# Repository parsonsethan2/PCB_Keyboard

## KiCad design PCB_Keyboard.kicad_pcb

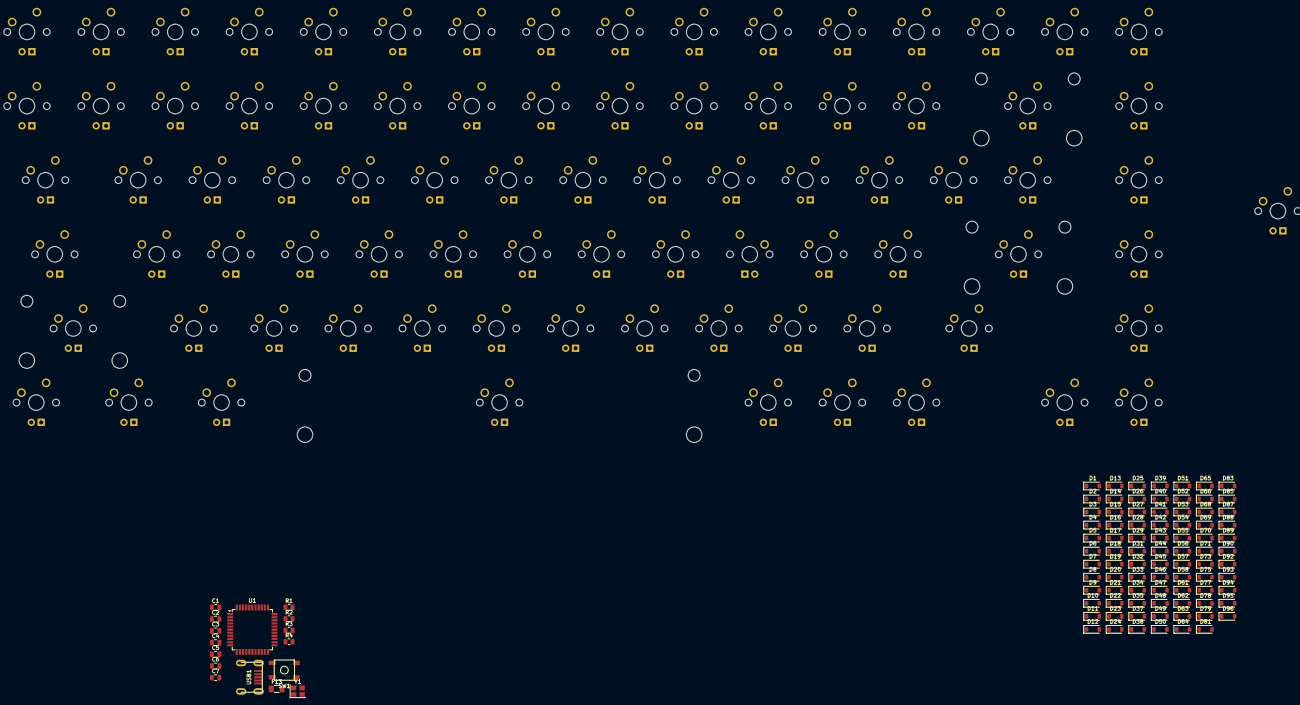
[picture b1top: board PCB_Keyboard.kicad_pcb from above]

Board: 2 copper layers, 182 parts (1 on the bottom side), 116 nets, no tracks yet.

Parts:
+/=1: MX-NoLED; MXOnly-1U
-/_1: MX-NoLED; MXOnly-1U
Backspace1: MX-NoLED; MXOnly-2U
C1: 1uF; C_0805_2012Metric
C2, C3, C4: 0.1uF; C_0805_2012Metric
C5: 10uF; C_0805_2012Metric
C6, C7: 22pF; C_0805_2012Metric
D1, D2, D3, D4, D5, D6, D7, D8, D9, D10, D11, D12, D13, D14, D15, D16, D17, D18, D19, D20, D21, D22, D23, D24, D25, D26, D27, D28, D29, D31, D32, D33, D34, D35, D37, D38, D39, D40, D41, D42, D43, D44, D45, D46, D47, D48, D49, D50, D51, D52, D53, D54, D55, D56, D57, D58, D61, D62, D63, D64, D65, D66, D68, D69, D70, D71, D73, D75, D77, D78, D79, D81, D83, D85, D87, D88, D89, D90, D92, D93, D94, D95, D96: D_Small; D_SOD-123
Delete/Insert1: MX-NoLED; MXOnly-1U
F13: 500mA; Fuse_1206_3216Metric
Home1: MX-NoLED; MXOnly-1U
MX."1, MX.:1, MX.<1, MX.>1, MX.?, MX.A1, MX.B1, MX.C1, MX.Command2, MX.Ctrl2, MX.D1, MX.E1, MX.End1, MX.F1, MX.Fn1, MX.G1, MX.H1, MX.I1, MX.J1, MX.K1, MX.L1, MX.M1, MX.N1, MX.O1, MX.P1, MX.PageDown1, MX.Q1, MX.R1, MX.S1, MX.T1, MX.Tilda1, MX.U1, MX.V1, MX.W1, MX.X1, MX.Y1, MX.Z1, MX.backslash1, MX.down1, MX.right1, MX.up1, MX.{1, MX.}1: MX-NoLED; MXOnly-1U
MX.CapsLock1, MX.ShiftHalf1: MX-NoLED; MXOnly-1.75U
MX.Command1, MX.Ctrl1, MX.Option1: MX-NoLED; MXOnly-1.25U
MX.Enter1, MX.ShiftFull1: MX-NoLED; MXOnly-2.25U
MX.TabFull1: MX-NoLED; MXOnly-1.5U
MXNum.1, MXNum.2, MXNum.3, MXNum.4, MXNum.5, MXNum.6, MXNum.7, MXNum.8: MX-NoLED; MXOnly-1U
NmLck1: MX-NoLED; MXOnly-1U
Num.0, Num.9: MX-NoLED; MXOnly-1U
Pageup1: MX-NoLED; MXOnly-1U
R1, R4: 10k; R_0805_2012Metric
R2, R3: 22; R_0805_2012Metric
SW1: SW_Push; SKQG-1155865
ScrLk1: MX-NoLED; MXOnly-1U
Spacebar1: MX-NoLED; MXOnly-6.25U
U1: ATmega32U4-A; TQFP-44_10x10mm_P0.8mm
USB1: Molex-0548190589
Y1: 16MHz; Crystal_SMD_3225-4Pin_3.2x2.5mm
esc1: MX-NoLED; MXOnly-1U
f1, f2, f3, f4, f5, f6, f7, f8, f9, f10, f11, f12: MX-NoLED; MXOnly-1U

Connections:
+5V: C2.1, C3.1, C4.1, C5.1, F13.2, R4.2, U1.2 (UVCC), U1.7 (VBUS), U1.14 (VCC), U1.24 (AVCC), U1.34 (VCC), U1.44 (AVCC)
/D+: R2.1, USB1.3 (D+)
/D-: R3.1, USB1.4 (D-)
/matrix/col0: MX.CapsLock1.1 (COL), MX.Ctrl1.1 (COL), MX.ShiftFull1.1 (COL), MX.TabFull1.1 (COL), MX.Tilda1.1 (COL), esc1.1 (COL)
/matrix/col1: MX.Option1.1 (COL), MX.Q1.1 (COL), MXNum.1.1 (COL), f1.1 (COL)
/matrix/col2: MX.A1.1 (COL), MX.Command1.1 (COL), MX.W1.1 (COL), MX.Z1.1 (COL), MXNum.2.1 (COL), f2.1 (COL)
/matrix/col3: MX.E1.1 (COL), MX.S1.1 (COL), MX.X1.1 (COL), MXNum.3.1 (COL), f3.1 (COL)
/matrix/col4: MX.C1.1 (COL), MX.D1.1 (COL), MX.R1.1 (COL), MXNum.4.1 (COL), f4.1 (COL)
/matrix/col5: MX.F1.1 (COL), MX.T1.1 (COL), MX.V1.1 (COL), MXNum.5.1 (COL), f5.1 (COL)
/matrix/col6: MX.B1.1 (COL), MX.G1.1 (COL), MX.Y1.1 (COL), MXNum.6.1 (COL), Spacebar1.1 (COL), f6.1 (COL)
/matrix/col7: MX.H1.1 (COL), MX.N1.1 (COL), MX.U1.1 (COL), MXNum.7.1 (COL), f7.1 (COL)
/matrix/col8: MX.I1.1 (COL), MX.J1.1 (COL), MX.M1.1 (COL), MXNum.8.1 (COL), f8.1 (COL)
/matrix/col9: MX.<1.1 (COL), MX.K1.1 (COL), MX.O1.1 (COL), Num.9.1 (COL), f9.1 (COL)
/matrix/col10: MX.>1.1 (COL), MX.L1.1 (COL), MX.P1.1 (COL), Num.0.1 (COL), f10.1 (COL)
/matrix/col11: -/_1.1 (COL), MX.:1.1 (COL), MX.?.1 (COL), MX.Command2.1 (COL), MX.{1.1 (COL), f11.1 (COL)
/matrix/col12: +/=1.1 (COL), MX."1.1 (COL), MX.Fn1.1 (COL), MX.ShiftHalf1.1 (COL), MX.}1.1 (COL), f12.1 (COL)
/matrix/col13: MX.Ctrl2.1 (COL), NmLck1.1 (COL)
/matrix/col14: Backspace1.1 (COL), MX.Enter1.1 (COL), MX.backslash1.1 (COL), MX.down1.1 (COL), MX.up1.1 (COL), ScrLk1.1 (COL)
/matrix/col15: Delete/Insert1.1 (COL), Home1.1 (COL), MX.End1.1 (COL), MX.PageDown1.1 (COL), MX.right1.1 (COL), Pageup1.1 (COL)
/matrix/row0: D1.1 (K), D2.1 (K), D3.1 (K), D4.1 (K), D5.1 (K), D6.1 (K), D7.1 (K), D8.1 (K), D9.1 (K), D10.1 (K), D11.1 (K), D12.1 (K), D13.1 (K), D14.1 (K), D15.1 (K), D16.1 (K)
/matrix/row1: D17.1 (K), D18.1 (K), D19.1 (K), D20.1 (K), D21.1 (K), D22.1 (K), D23.1 (K), D24.1 (K), D25.1 (K), D26.1 (K), D27.1 (K), D28.1 (K), D29.1 (K), D31.1 (K), D32.1 (K)
/matrix/row2: D33.1 (K), D35.1 (K), D37.1 (K), D39.1 (K), D41.1 (K), D43.1 (K), D45.1 (K), D47.1 (K), D49.1 (K), D51.1 (K), D53.1 (K), D55.1 (K), D57.1 (K), D61.1 (K), D63.1 (K)
/matrix/row3: D34.1 (K), D38.1 (K), D40.1 (K), D42.1 (K), D44.1 (K), D46.1 (K), D48.1 (K), D50.1 (K), D52.1 (K), D54.1 (K), D56.1 (K), D58.1 (K), D62.1 (K), D64.1 (K)
/matrix/row4: D65.1 (K), D69.1 (K), D71.1 (K), D73.1 (K), D75.1 (K), D77.1 (K), D79.1 (K), D81.1 (K), D83.1 (K), D85.1 (K), D87.1 (K), D89.1 (K), D93.1 (K), D95.1 (K)
/matrix/row5: D66.1 (K), D68.1 (K), D70.1 (K), D78.1 (K), D88.1 (K), D90.1 (K), D92.1 (K), D94.1 (K), D96.1 (K)
GND: C1.2, C2.2, C3.2, C4.2, C5.2, C6.1, C7.1, R1.2, SW1.1, U1.5 (UGND), U1.15 (GND), U1.23 (GND), U1.35 (GND), U1.43 (GND), USB1.1 (GND), Y1.2, Y1.4
unnamed: +/=1.2 (ROW), D29.2 (A)
unnamed: -/_1.2 (ROW), D28.2 (A)
unnamed: Backspace1.2 (ROW), D31.2 (A)
unnamed: D1.2 (A), esc1.2 (ROW)
unnamed: D2.2 (A), f1.2 (ROW)
unnamed: D3.2 (A), f2.2 (ROW)
unnamed: D4.2 (A), f3.2 (ROW)
unnamed: D5.2 (A), f4.2 (ROW)
unnamed: D6.2 (A), f5.2 (ROW)
unnamed: D7.2 (A), f6.2 (ROW)
unnamed: D8.2 (A), f7.2 (ROW)
unnamed: D9.2 (A), f8.2 (ROW)
unnamed: D10.2 (A), f9.2 (ROW)
unnamed: D11.2 (A), f10.2 (ROW)
unnamed: D12.2 (A), f11.2 (ROW)
unnamed: D13.2 (A), f12.2 (ROW)
unnamed: D14.2 (A), NmLck1.2 (ROW)
unnamed: D15.2 (A), ScrLk1.2 (ROW)
unnamed: D16.2 (A), Delete/Insert1.2 (ROW)
unnamed: D17.2 (A), MX.Tilda1.2 (ROW)
unnamed: D18.2 (A), MXNum.1.2 (ROW)
unnamed: D19.2 (A), MXNum.2.2 (ROW)
unnamed: D20.2 (A), MXNum.3.2 (ROW)
unnamed: D21.2 (A), MXNum.4.2 (ROW)
unnamed: D22.2 (A), MXNum.5.2 (ROW)
unnamed: D23.2 (A), MXNum.6.2 (ROW)
unnamed: D24.2 (A), MXNum.7.2 (ROW)
unnamed: D25.2 (A), MXNum.8.2 (ROW)
unnamed: D26.2 (A), Num.9.2 (ROW)
unnamed: D27.2 (A), Num.0.2 (ROW)
unnamed: D32.2 (A), Home1.2 (ROW)
unnamed: D33.2 (A), MX.TabFull1.2 (ROW)
unnamed: D34.2 (A), MX.CapsLock1.2 (ROW)
unnamed: D35.2 (A), MX.Q1.2 (ROW)
unnamed: D37.2 (A), MX.W1.2 (ROW)
unnamed: D38.2 (A), MX.A1.2 (ROW)
unnamed: D39.2 (A), MX.E1.2 (ROW)
unnamed: D40.2 (A), MX.S1.2 (ROW)
unnamed: D41.2 (A), MX.R1.2 (ROW)
unnamed: D42.2 (A), MX.D1.2 (ROW)
unnamed: D43.2 (A), MX.T1.2 (ROW)
unnamed: D44.2 (A), MX.F1.2 (ROW)
unnamed: D45.2 (A), MX.Y1.2 (ROW)
unnamed: D46.2 (A), MX.G1.2 (ROW)
unnamed: D47.2 (A), MX.U1.2 (ROW)
unnamed: D48.2 (A), MX.H1.2 (ROW)
unnamed: D49.2 (A), MX.I1.2 (ROW)
unnamed: D50.2 (A), MX.J1.2 (ROW)
unnamed: D51.2 (A), MX.O1.2 (ROW)
unnamed: D52.2 (A), MX.K1.2 (ROW)
unnamed: D53.2 (A), MX.P1.2 (ROW)
unnamed: D54.2 (A), MX.L1.2 (ROW)
unnamed: D55.2 (A), MX.{1.2 (ROW)
unnamed: D56.2 (A), MX.:1.2 (ROW)
unnamed: D57.2 (A), MX.}1.2 (ROW)
unnamed: D58.2 (A), MX."1.2 (ROW)
unnamed: D61.2 (A), MX.backslash1.2 (ROW)
unnamed: D62.2 (A), MX.Enter1.2 (ROW)
unnamed: D63.2 (A), Pageup1.2 (ROW)
unnamed: D64.2 (A), MX.PageDown1.2 (ROW)
unnamed: D65.2 (A), MX.ShiftFull1.2 (ROW)
unnamed: D66.2 (A), MX.Ctrl1.2 (ROW)
unnamed: D68.2 (A), MX.Option1.2 (ROW)
unnamed: D69.2 (A), MX.Z1.2 (ROW)
unnamed: D70.2 (A), MX.Command1.2 (ROW)
unnamed: D71.2 (A), MX.X1.2 (ROW)
unnamed: D73.2 (A), MX.C1.2 (ROW)
unnamed: D75.2 (A), MX.V1.2 (ROW)
unnamed: D77.2 (A), MX.B1.2 (ROW)
unnamed: D78.2 (A), Spacebar1.2 (ROW)
unnamed: D79.2 (A), MX.N1.2 (ROW)
unnamed: D81.2 (A), MX.M1.2 (ROW)
unnamed: D83.2 (A), MX.<1.2 (ROW)
unnamed: D85.2 (A), MX.>1.2 (ROW)
unnamed: D87.2 (A), MX.?.2 (ROW)
unnamed: D88.2 (A), MX.Command2.2 (ROW)
unnamed: D89.2 (A), MX.ShiftHalf1.2 (ROW)
unnamed: D90.2 (A), MX.Fn1.2 (ROW)
unnamed: D92.2 (A), MX.Ctrl2.2 (ROW)
unnamed: D93.2 (A), MX.up1.2 (ROW)
unnamed: D94.2 (A), MX.down1.2 (ROW)
unnamed: D95.2 (A), MX.End1.2 (ROW)
unnamed: D96.2 (A), MX.right1.2 (ROW)
unnamed: R2.2, U1.4 (D+)
unnamed: R3.2, U1.3 (D-)
unnamed: C1.1, U1.6 (UCAP)
unnamed: C7.2, U1.17 (XTAL1), Y1.1
unnamed: C6.2, U1.16 (XTAL2), Y1.3
unnamed: R1.1, U1.33 (~HWB/PE2)
unnamed: R4.1, SW1.2, U1.13 (~RESET)

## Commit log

2025-01-11 Add submodules
2025-01-11 Kicad Project Libraries
    MX Switches Footprints and 3D models.
2025-01-21 Switches and Schematic
    Updated the switch matrix and connections for the ATMEGA
2025-02-08 Add Type-C Submodule
